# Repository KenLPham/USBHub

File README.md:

[Bill of Materials](https://www.mouser.com/ProjectManager/ProjectDetail.aspx?AccessID=672a76c6ab)

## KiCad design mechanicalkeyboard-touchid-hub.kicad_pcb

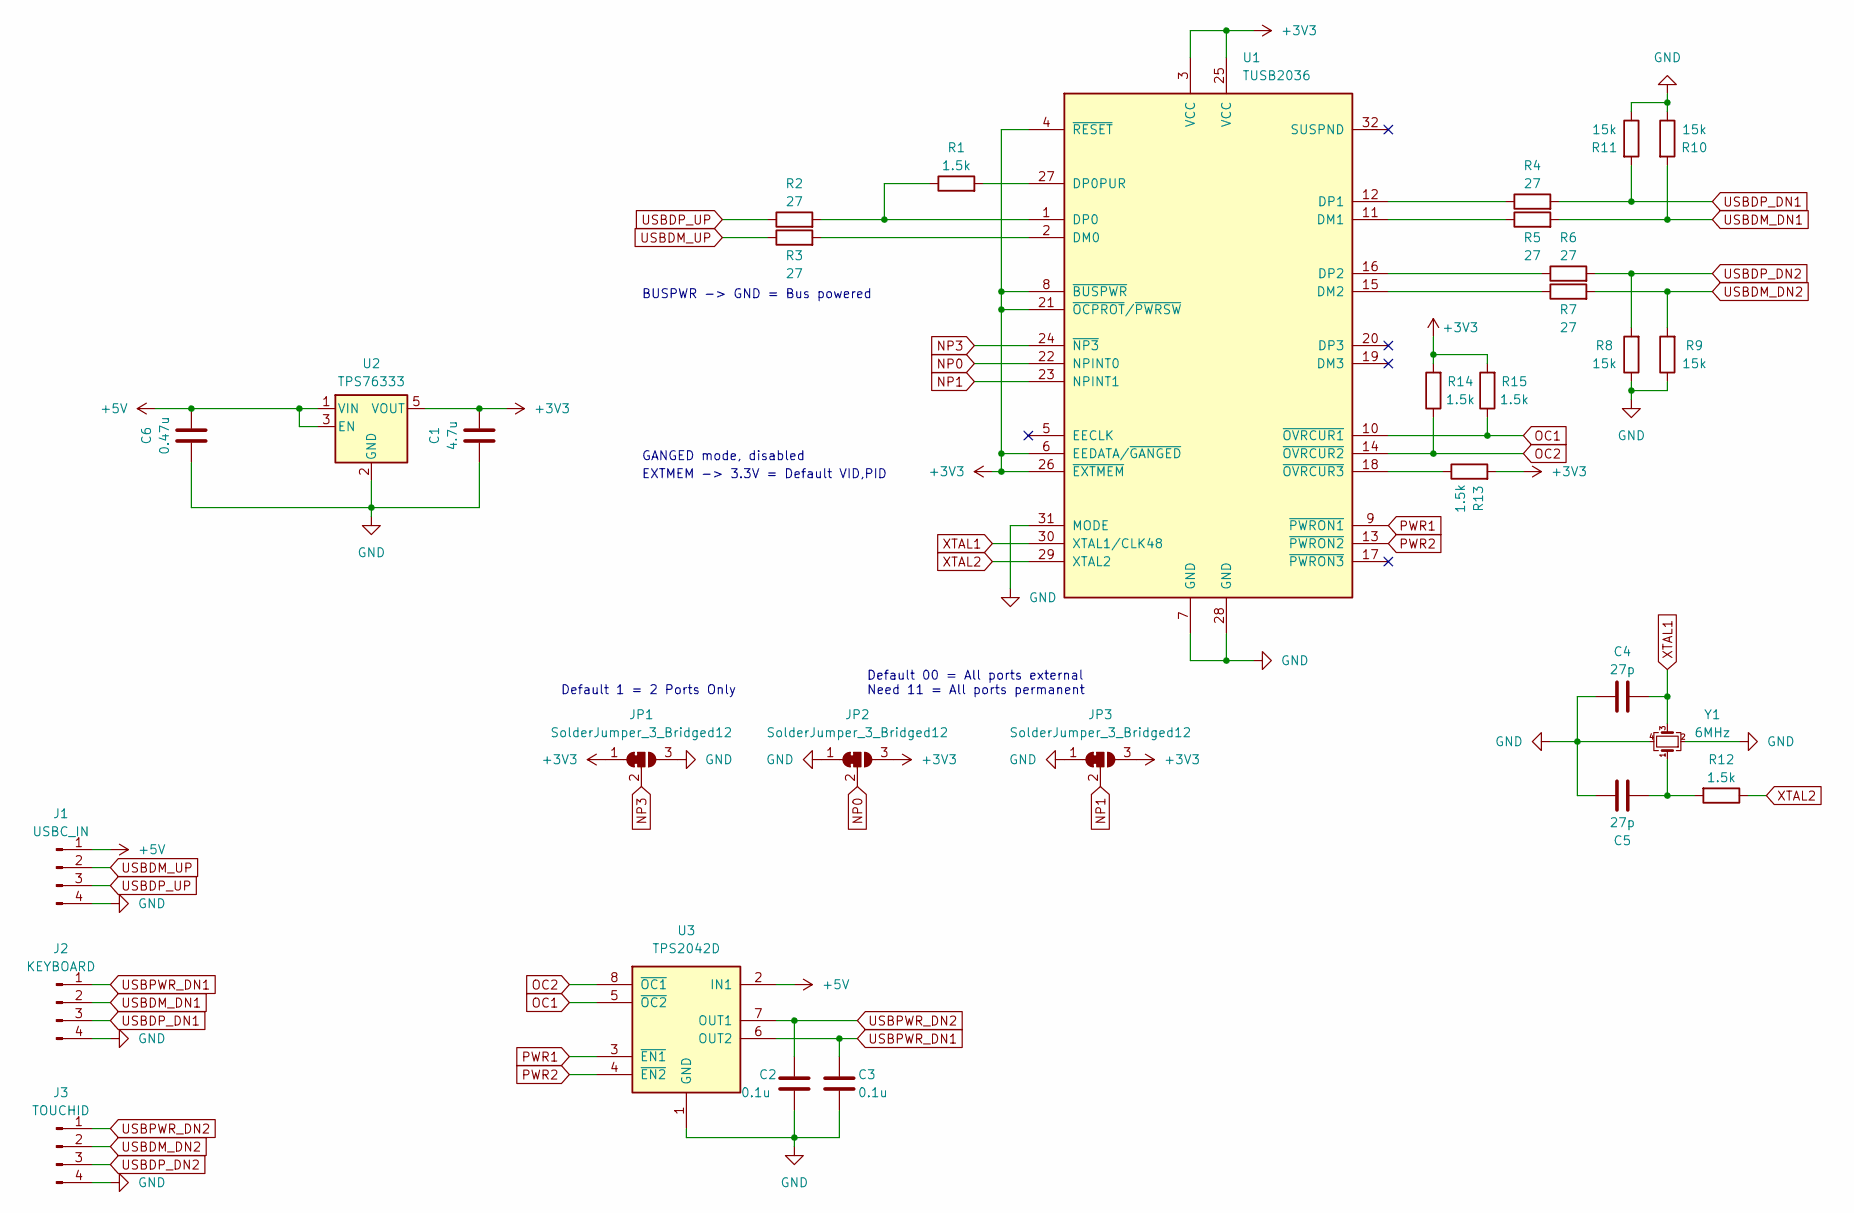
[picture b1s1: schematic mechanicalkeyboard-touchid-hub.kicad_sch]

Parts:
C1: 4.7u; C_0603_1608Metric_Pad1.08x0.95mm_HandSolder
C2, C3: 0.1u; C_0603_1608Metric_Pad1.08x0.95mm_HandSolder
C4, C5: 27p; C_0603_1608Metric_Pad1.08x0.95mm_HandSolder
C6: 0.47u; C_0603_1608Metric_Pad1.08x0.95mm_HandSolder
J1: USBC_IN; SolderWire-0.1sqmm_1x04_P3.6mm_D0.4mm_OD1mm
J2: KEYBOARD; SolderWire-0.1sqmm_1x04_P3.6mm_D0.4mm_OD1mm
J3: TOUCHID; SolderWire-0.1sqmm_1x04_P3.6mm_D0.4mm_OD1mm
JP1, JP2, JP3: SolderJumper_3_Bridged12; SolderJumper-3_P1.3mm_Bridged12_Pad1.0x1.5mm_NumberLabels
R1, R12, R13, R14, R15: 1.5k; R_0603_1608Metric_Pad0.98x0.95mm_HandSolder
R2, R3, R4, R5, R6, R7: 27; R_0603_1608Metric_Pad0.98x0.95mm_HandSolder
R8, R9, R10, R11: 15k; R_0603_1608Metric_Pad0.98x0.95mm_HandSolder
U1: TUSB2036; LQFP-32_7x7mm_P0.8mm
U2: TPS76333; SOT-23-5
U3: TPS2042D; SOIC-8_3.9x4.9mm_P1.27mm
Y1: 6MHz; Crystal_SMD_7050-4Pin_7.0x5.0mm

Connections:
+3V3: C1.1, JP1.1 (A), JP2.3 (B), JP3.3 (B), R13.2, R14.2, R15.2, U1.3 (VCC), U1.4 (~RESET), U1.6 (EEDATA/~GANGED), U1.8 (~BUSPWR), U1.21 (~OCPROT/~PWRSW), U1.25 (VCC), U1.26 (~EXTMEM), U2.5 (VOUT)
+5V: C6.2, J1.1, U2.1 (VIN), U2.3 (EN), U3.2 (IN1)
GND: C1.2, C2.2, C3.2, C4.1, C5.1, C6.1, J1.4, J2.4, J3.4, JP1.3 (B), JP2.1 (A), JP3.1 (A), R8.1, R9.1, R10.1, R11.1, U1.7 (GND), U1.28 (GND), U1.31 (MODE), U2.2 (GND), U3.1 (GND), Y1.2, Y1.4
NP0: JP2.2 (C), U1.22 (NPINT0)
NP1: JP3.2 (C), U1.23 (NPINT1)
NP3: JP1.2 (C), U1.24 (~NP3)
unnamed: C5.2, R12.2, Y1.1
unnamed: R3.2, U1.2 (DM0)
unnamed: R5.1, U1.11 (DM1)
unnamed: R7.1, U1.15 (DM2)
unnamed: R1.1, R2.2, U1.1 (DP0)
unnamed: R1.2, U1.27 (DP0PUR)
unnamed: R4.1, U1.12 (DP1)
unnamed: R6.1, U1.16 (DP2)
unnamed: R13.1, U1.18 (~OVRCUR3)
OC1: R15.1, U1.10 (~OVRCUR1), U3.5 (~OC2)
OC2: R14.1, U1.14 (~OVRCUR2), U3.8 (~OC1)
PWR1: U1.9 (~PWRON1), U3.3 (~EN1)
PWR2: U1.13 (~PWRON2), U3.4 (~EN2)
USBDM_DN1: J2.2, R5.2, R10.2
USBDM_DN2: J3.2, R7.2, R9.2
USBDM_UP: J1.2, R3.1
USBDP_DN1: J2.3, R4.2, R11.2
USBDP_DN2: J3.3, R6.2, R8.2
USBDP_UP: J1.3, R2.1
USBPWR_DN1: C3.1, J2.1, U3.6 (OUT2)
USBPWR_DN2: C2.1, J3.1, U3.7 (OUT1)
XTAL1: C4.2, U1.30 (XTAL1/CLK48), Y1.3
XTAL2: R12.1, U1.29 (XTAL2)

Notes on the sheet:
Default 1 = 2 Ports Only
GANGED mode, disabled
Default 00 = All ports external Need 11 = All ports permanent
BUSPWR -> GND = Bus powered
EXTMEM -> 3.3V = Default VID,PID

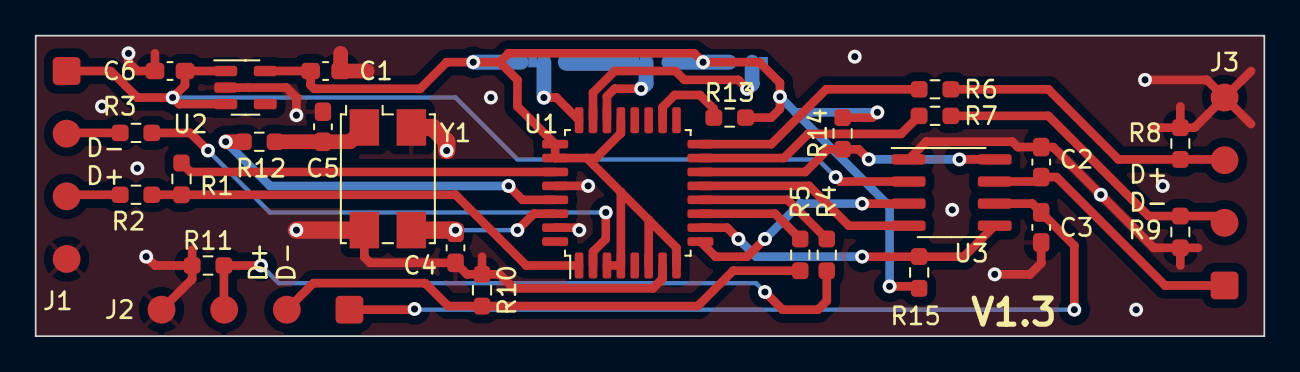
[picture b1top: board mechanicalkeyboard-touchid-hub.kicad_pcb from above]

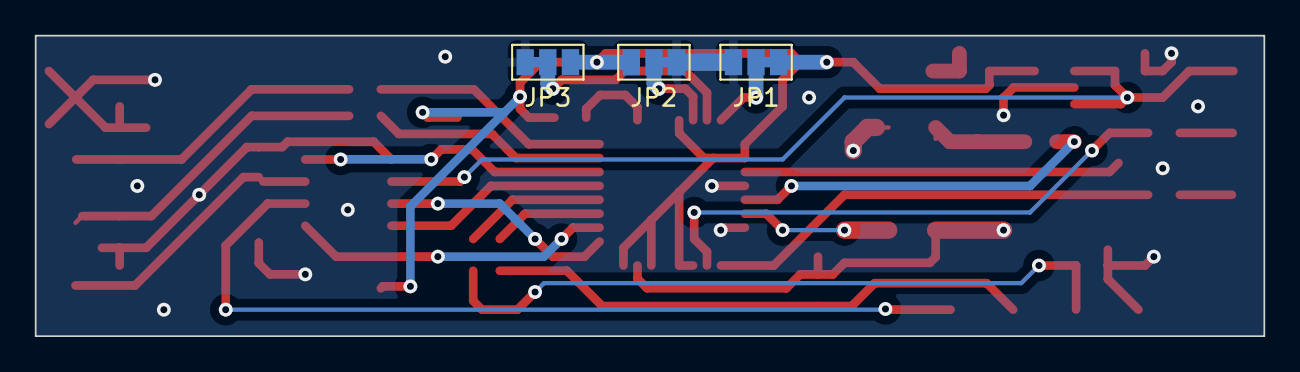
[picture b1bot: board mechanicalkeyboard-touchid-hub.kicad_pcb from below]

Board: 2 copper layers, 70.6 x 17.3 mm, 31 parts (3 on the bottom side), 29 nets.

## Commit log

2024-05-10 Create README.md
    Add BOM
